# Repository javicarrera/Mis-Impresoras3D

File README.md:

# Mis-Impresoras3D
Recursos para mis impresoras

Para recursos que ocupen mucho hay que proceder de otra forma, a través de la Git Large File Storage. 

1. Instalar https://git-lfs.github.com/
2. Iniciar git lfs 'git lfs install'
   
Hasta aquí se hace para cada cuenta de usuario 
A partir de ahora en cada repositorio hay que seleccionar el tipo de arquivos que quieres que maneje el LFS

'git lfs track "*.psd"'
'git lfs track "*.STEP"'
...
Añadir a git el archivo .gitattributes que ha sido creado automáticamente:
'git add .gitattributes'

Commit & push a Github como siempre...
'''
git add file.psd
git commit -m "Add design file"
git push origin main
'''

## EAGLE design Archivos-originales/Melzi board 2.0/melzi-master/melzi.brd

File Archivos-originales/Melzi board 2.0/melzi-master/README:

Melzi Ardentissimo
Based on Sanguinololu

Schematic and board files.

http://reprap.org/wiki/Melzi

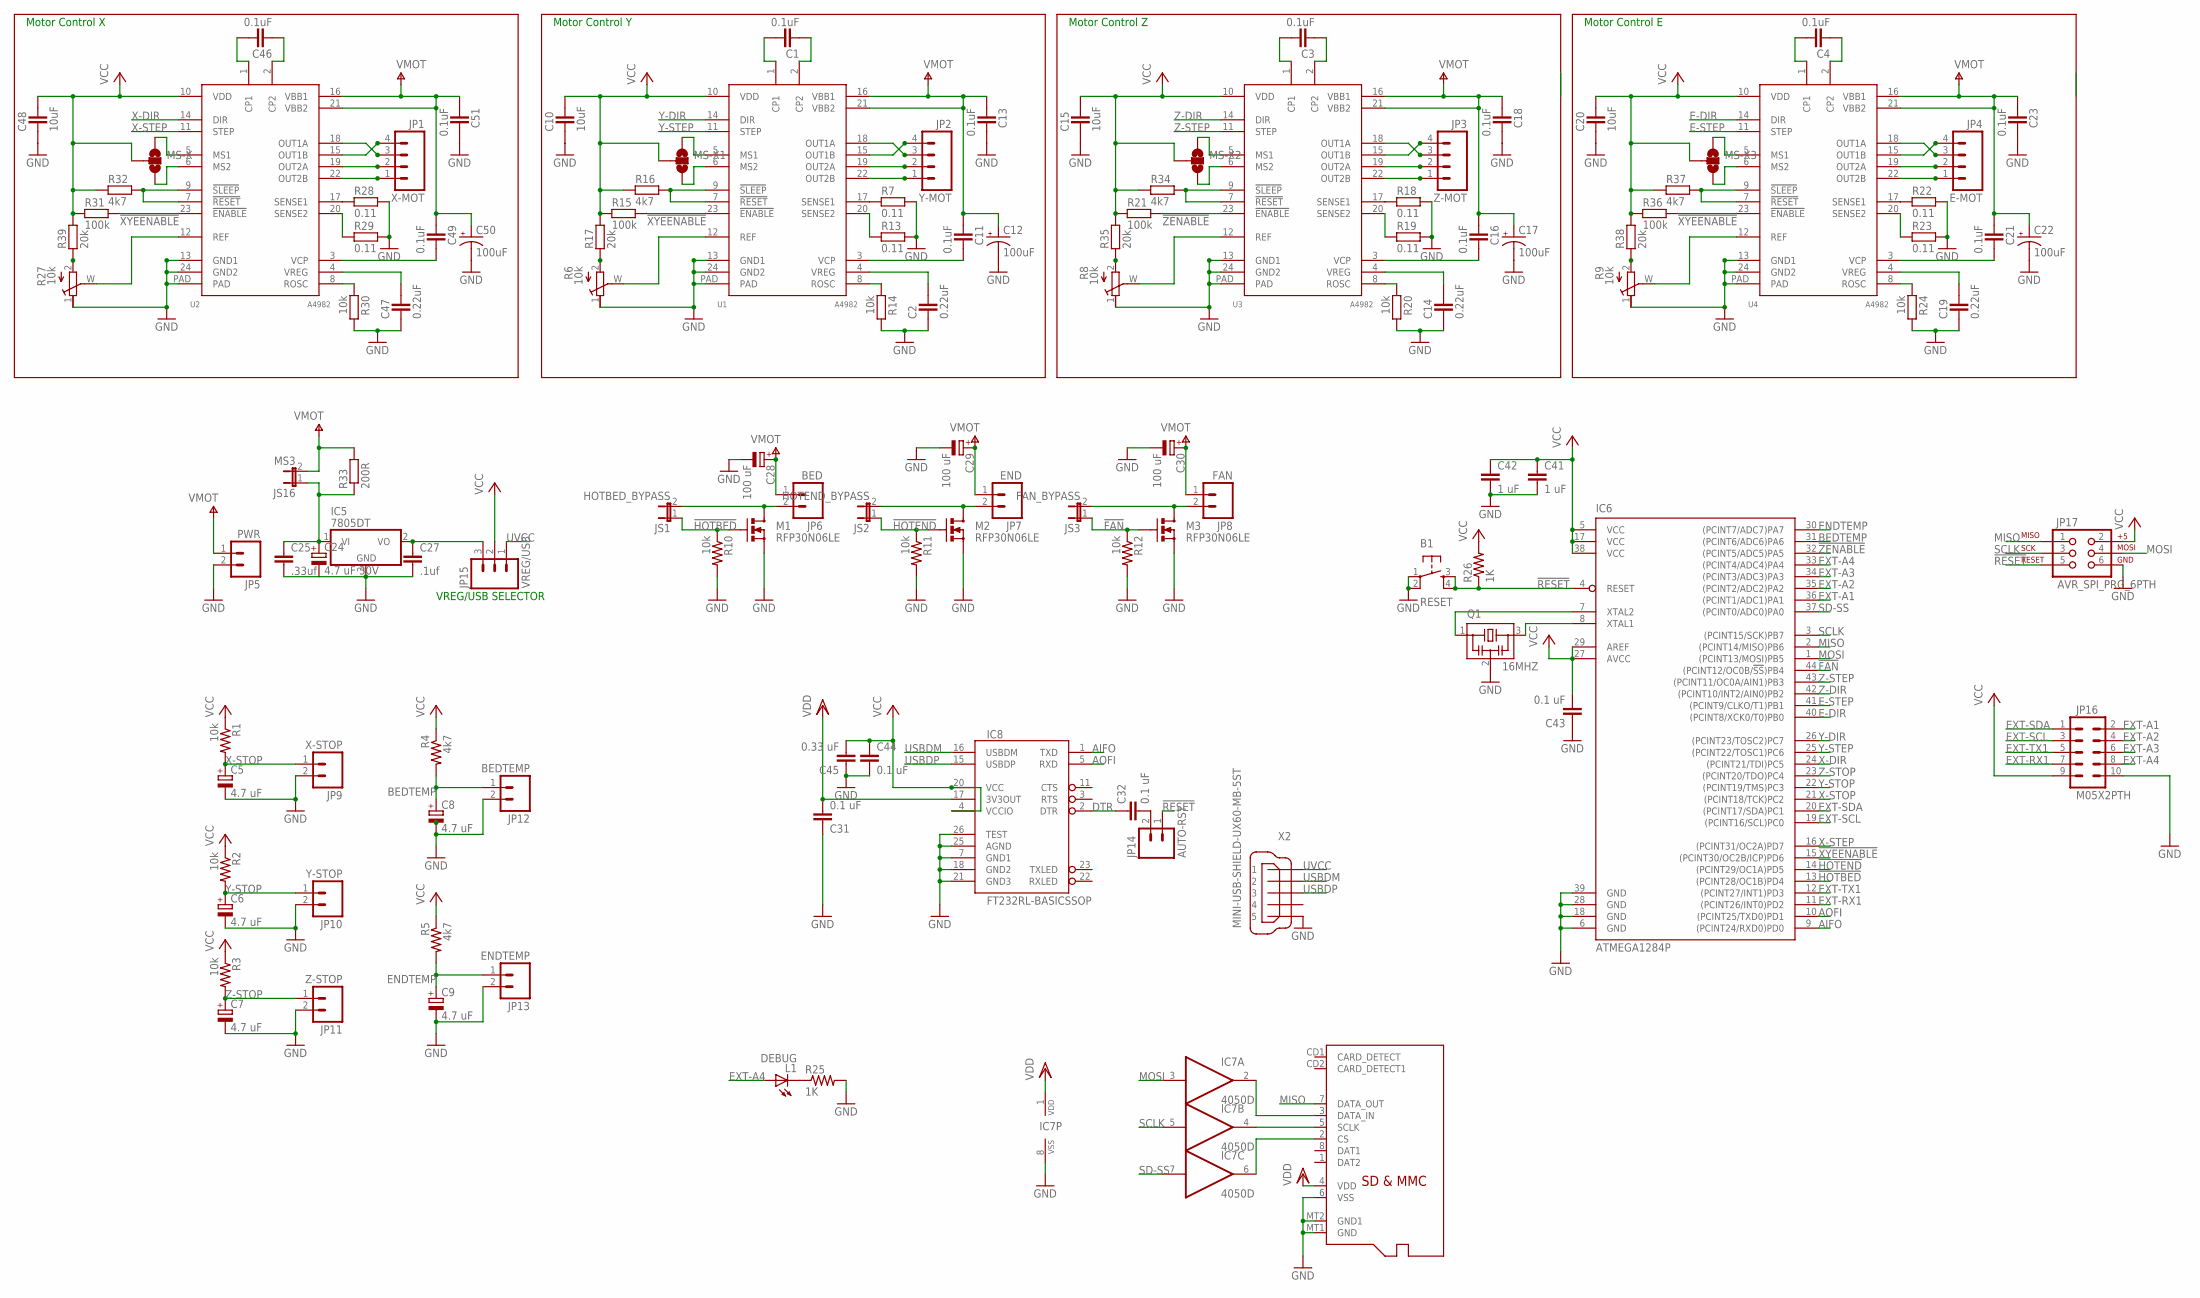
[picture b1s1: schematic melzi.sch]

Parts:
B1: RESET; TACTILE_SWITCH_SMD
C1, C3, C4, C11, C13, C16, C18, C21, C23, C46, C49, C51: 0.1uF; CAPC2012X145AN
C2, C14, C19, C47: 0.22uF; CAPC2012X145AN
C5, C6, C7, C8, C9: 4.7 uF; SMC_C
C10, C15, C20, C48: 10uF; CAPC2012X145AN
C12, C17, C22, C50: 100uF; PANASONIC_D
C24: 4.7 uF 30V; SMC_C
C25: .33uf; 0805
C27: .1uf; 0805
C28, C29, C30: 100 uF; UD-6,3X7,7_NICHICON
C31, C32, C43, C44: 0.1 uF; C1206
C41, C42: 1 uF; C1206
C45: 0.33 uF; C1206
IC5: 7805DT; TO252
IC6: ATMEGA1284P; TQFP44
IC7: 4050D; SO16
IC8: FT232RL-BASICSSOP; SSOP28DB
JP1: X-MOT; SCREWTERMINAL-3.5MM-4
JP2: Y-MOT; SCREWTERMINAL-3.5MM-4
JP3: Z-MOT; SCREWTERMINAL-3.5MM-4
JP4: E-MOT; SCREWTERMINAL-3.5MM-4
JP5: PWR; SCREWTERMINAL-5MM-2
JP6: BED; SCREWTERMINAL-5MM-2
JP7: END; SCREWTERMINAL-5MM-2
JP8: FAN; SCREWTERMINAL-5MM-2
JP9: X-STOP; SCREWTERMINAL-3.5MM-2
JP10: Y-STOP; SCREWTERMINAL-3.5MM-2
JP11: Z-STOP; SCREWTERMINAL-3.5MM-2
JP12: BEDTEMP; SCREWTERMINAL-3.5MM-2
JP13: ENDTEMP; SCREWTERMINAL-3.5MM-2
JP14: AUTO-RST; 1X02
JP15: VREG/USB; 1X03
JP16: M05X2PTH; AVR_ICSP
JP17: AVR_SPI_PRG_6PTH; 2X3
JS1: HOTBED_BYPASS; SJ_2S-NO
JS2: HOTEND_BYPASS; SJ_2S-NO
JS3: FAN_BYPASS; SJ_2S-NO
JS16: MS3; SJ_2S
L1: DEBUG; LED-1206
M1, M2, M3: RFP30N06LE; DPAK
MS-X, MS-X1, MS-X2, MS-X3: SOLDERJUMPER_2WAYCONNECTED; SJ_3_CONNECTED
Q1: 16MHZ; CSTCR6M
R1, R2, R3, R10, R11, R12: 10k; 1206
R4, R5: 4k7; 1206
R6, R8, R9, R27: 10k; RTRIM-ST4ETB
R7, R13, R18, R19, R22, R23, R28, R29: 0.11; RESC2012X70N
R14, R20, R24, R30: 10k; RESC2012X70N
R15, R21, R31, R36: 100k; RESC2012X70N
R16, R32, R34, R37: 4k7; RESC2012X70N
R17, R35, R38, R39: 20k; RESC2012X70N
R25, R26: 1K; 1206
R33: 200R; 0309V
U1, U2, U3, U4: A4982; TSSOP-24
X1: MICROSD
X2: MINI-USB-SHIELD-UX60-MB-5ST; UX60-MB-5ST

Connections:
!FAN: IC6.44 ((PCINT12/OC0B/!SS!)PB4), JS3.1, M3.1 (G), R12.1
!HOTBED: IC6.13 ((PCINT28/OC1B)PD4), JS1.1, M1.1 (G), R10.1
!HOTEND: IC6.14 ((PCINT29/OC1A)PD5), JS2.1, M2.1 (G), R11.1
!RESET: B1.3, B1.4, IC6.4 (RESET), JP14.1, JP17.5, R26.1
!XYEENABLE: IC6.15 ((PCINT30/OC2B/ICP)PD6), R15.2, R31.2, R36.2, U1.23 (!ENABLE), U2.23 (!ENABLE), U4.23 (!ENABLE)
!ZENABLE: IC6.32 ((PCINT5/ADC5)PA5), R21.2, U3.23 (!ENABLE)
AIFO: IC6.9 ((PCINT24/RXD0)PD0), IC8.1 (TXD)
AOFI: IC6.10 ((PCINT25/TXD0)PD1), IC8.5 (RXD)
BEDTEMP: C8.+, IC6.31 ((PCINT6/ADC6)PA6), JP12.1, R4.2
DTR: C32.1, IC8.2 (DTR)
E-DIR: IC6.40 ((PCINT8/XCK0/T0)PB0), U4.14 (DIR)
E-STEP: IC6.41 ((PCINT9/CLKO/T1)PB1), U4.11 (STEP)
ENDTEMP: C9.+, IC6.30 ((PCINT7/ADC7)PA7), JP13.1, R5.2
EXT-A1: IC6.36 ((PCINT1/ADC1)PA1), JP16.2
EXT-A2: IC6.35 ((PCINT2/ADC2)PA2), JP16.4
EXT-A3: IC6.34 ((PCINT3/ADC3)PA3), JP16.6
EXT-A4: IC6.33 ((PCINT4/ADC4)PA4), JP16.8, L1.A
EXT-RX1: IC6.11 ((PCINT26/INT0)PD2), JP16.7
EXT-SCL: IC6.19 ((PCINT16/SCL)PC0), JP16.3
EXT-SDA: IC6.20 ((PCINT17/SDA)PC1), JP16.1
EXT-TX1: IC6.12 ((PCINT27/INT1)PD3), JP16.5
GND: B1.1, B1.2, C2.1, C5.-, C6.-, C7.-, C8.-, C9.-, C10.1, C12.-, C13.2, C14.1, C15.1, C17.-, C18.2, C19.1, C20.1, C22.-, C23.2, C24.-, C25.2, C27.2, C28.-, C29.-, C30.-, C31.1, C41.2, C42.2, C43.1, C44.2, C45.1, C47.1, C48.1, C50.-, C51.2, IC5.3 (GND), IC6.6 (GND), IC6.18 (GND), IC6.28 (GND), IC6.39 (GND), IC7.8 (VSS), IC8.7 (GND1), IC8.18 (GND2), IC8.21 (GND3), IC8.25 (AGND), IC8.26 (TEST), JP5.2, JP9.2, JP10.2, JP11.2, JP12.2, JP13.2, JP16.10, JP17.6, M1.3 (S), M2.3 (S), M3.3 (S), Q1.2, R6.1 (A), R7.2, R8.1 (A), R9.1 (A), R10.2, R11.2, R12.2, R13.2, R14.2, R18.2, R19.2, R20.2, R22.2, R23.2, R24.2, R25.2, R27.1 (A), R28.2, R29.2, R30.2, U1.13 (GND1), U1.24 (GND2), U1.PAD, U2.13 (GND1), U2.24 (GND2), U2.PAD, U3.13 (GND1), U3.24 (GND2), U3.PAD, U4.13 (GND1), U4.24 (GND2), U4.PAD, X1.6 (VSS), X1.MT1 (GND), X1.MT2 (GND1), X2.5
HOTBED-GND: JP6.2, JS1.2, M1.4 (D)
HOTBED-GND1: JP7.2, JS2.2, M2.4 (D)
HOTBED-GND2: JP8.2, JS3.2, M3.4 (D)
MISO: IC6.2 ((PCINT14/MISO)PB6), JP17.1, X1.7 (DATA_OUT)
MOSI: IC6.1 ((PCINT13/MOSI)PB5), IC7.3 (I), JP17.4
unnamed: C46.2, U2.1 (CP1)
unnamed: L1.C, R25.1
unnamed: C1.2, U1.1 (CP1)
unnamed: C46.1, U2.2 (CP2)
unnamed: R28.1, U2.17 (SENSE1)
unnamed: R29.1, U2.20 (SENSE2)
unnamed: R27.W (S), U2.12 (REF)
unnamed: R30.1, U2.8 (ROSC)
unnamed: C47.2, U2.4 (VREG)
unnamed: R32.2, U2.7 (!RESET), U2.9 (!SLEEP)
unnamed: C1.1, U1.2 (CP2)
unnamed: IC7.2 (O), X1.3 (DATA_IN)
unnamed: IC7.4 (O), X1.5 (SCLK)
unnamed: IC7.6 (O), X1.2 (CS)
unnamed: C27.1, IC5.2 (VO), JP15.3
unnamed: R7.1, U1.17 (SENSE1)
unnamed: R13.1, U1.20 (SENSE2)
unnamed: R6.W (S), U1.12 (REF)
unnamed: R14.1, U1.8 (ROSC)
unnamed: C3.2, U3.1 (CP1)
unnamed: C3.1, U3.2 (CP2)
unnamed: R18.1, U3.17 (SENSE1)
unnamed: C49.2, U2.3 (VCP)
unnamed: C4.2, U4.1 (CP1)
unnamed: C32.2, JP14.2
unnamed: C4.1, U4.2 (CP2)
unnamed: IC6.7 (XTAL2), Q1.1
unnamed: IC6.8 (XTAL1), Q1.3
unnamed: MS-X.1, U2.5 (MS1)
unnamed: MS-X.3, U2.6 (MS2)
unnamed: JP1.3, U2.18 (OUT1A)
unnamed: JP1.4, U2.15 (OUT1B)
unnamed: JP1.2, U2.19 (OUT2A)
unnamed: JP1.1, U2.22 (OUT2B)
unnamed: C24.+, C25.1, IC5.1 (VI), JS16.1, R33.1
unnamed: C2.2, U1.4 (VREG)
unnamed: R16.2, U1.7 (!RESET), U1.9 (!SLEEP)
unnamed: C11.2, U1.3 (VCP)
unnamed: MS-X1.1, U1.5 (MS1)
unnamed: MS-X1.3, U1.6 (MS2)
unnamed: JP2.3, U1.18 (OUT1A)
unnamed: JP2.4, U1.15 (OUT1B)
unnamed: JP2.2, U1.19 (OUT2A)
unnamed: JP2.1, U1.22 (OUT2B)
unnamed: R6.2 (E), R17.1
unnamed: R19.1, U3.20 (SENSE2)
unnamed: R8.W (S), U3.12 (REF)
unnamed: R20.1, U3.8 (ROSC)
unnamed: C14.2, U3.4 (VREG)
unnamed: R34.2, U3.7 (!RESET), U3.9 (!SLEEP)
unnamed: C16.2, U3.3 (VCP)
unnamed: MS-X2.1, U3.5 (MS1)
unnamed: MS-X2.3, U3.6 (MS2)
unnamed: JP3.3, U3.18 (OUT1A)
unnamed: JP3.4, U3.15 (OUT1B)
unnamed: JP3.2, U3.19 (OUT2A)
unnamed: JP3.1, U3.22 (OUT2B)
unnamed: R8.2 (E), R35.1
unnamed: R22.1, U4.17 (SENSE1)
unnamed: R23.1, U4.20 (SENSE2)
unnamed: R9.W (S), U4.12 (REF)
unnamed: R24.1, U4.8 (ROSC)
unnamed: C19.2, U4.4 (VREG)
unnamed: R37.2, U4.7 (!RESET), U4.9 (!SLEEP)
unnamed: C21.2, U4.3 (VCP)
unnamed: MS-X3.1, U4.5 (MS1)
unnamed: MS-X3.3, U4.6 (MS2)
unnamed: R27.2 (E), R39.1
unnamed: JP4.3, U4.18 (OUT1A)
unnamed: JP4.4, U4.15 (OUT1B)
unnamed: JP4.2, U4.19 (OUT2A)
unnamed: JP4.1, U4.22 (OUT2B)
unnamed: R9.2 (E), R38.1
SCLK: IC6.3 ((PCINT15/SCK)PB7), IC7.5 (I), JP17.3
SD-SS: IC6.37 ((PCINT0/ADC0)PA0), IC7.7 (I)
USBDM: IC8.16 (USBDM), X2.2
USBDP: IC8.15 (USBDP), X2.3
UVCC: JP15.1, X2.1
VCC: C10.2, C15.2, C20.2, C41.1, C42.1, C43.2, C44.1, C45.2, C48.2, IC6.5 (VCC), IC6.17 (VCC), IC6.27 (AVCC), IC6.29 (AREF), IC6.38 (VCC), IC8.4 (VCCIO), IC8.20 (VCC), JP15.2, JP16.9, JP17.2, MS-X.2, MS-X1.2, MS-X2.2, MS-X3.2, R1.1, R2.1, R3.1, R4.1, R5.1, R15.1, R16.1, R17.2, R21.1, R26.2, R31.1, R32.1, R34.1, R35.2, R36.1, R37.1, R38.2, R39.2, U1.10 (VDD), U2.10 (VDD), U3.10 (VDD), U4.10 (VDD)
VDD: C31.2, IC7.1 (VDD), IC8.17 (3V3OUT), X1.4 (VDD)
VMOT: C11.1, C12.+, C13.1, C16.1, C17.+, C18.1, C21.1, C22.+, C23.1, C28.+, C29.+, C30.+, C49.1, C50.+, C51.1, JP5.1, JP6.1, JP7.1, JP8.1, JS16.2, R33.2, U1.16 (VBB1), U1.21 (VBB2), U2.16 (VBB1), U2.21 (VBB2), U3.16 (VBB1), U3.21 (VBB2), U4.16 (VBB1), U4.21 (VBB2)
X-DIR: IC6.24 ((PCINT21/TDI)PC5), U2.14 (DIR)
X-STEP: IC6.16 ((PCINT31/OC2A)PD7), U2.11 (STEP)
X-STOP: C5.+, IC6.21 ((PCINT18/TCK)PC2), JP9.1, R1.2
Y-DIR: IC6.26 ((PCINT23/TOSC2)PC7), U1.14 (DIR)
Y-STEP: IC6.25 ((PCINT22/TOSC1)PC6), U1.11 (STEP)
Y-STOP: C6.+, IC6.22 ((PCINT19/TMS)PC3), JP10.1, R2.2
Z-DIR: IC6.42 ((PCINT10/INT2/AIN0)PB2), U3.14 (DIR)
Z-STEP: IC6.43 ((PCINT11/OC0A/AIN1)PB3), U3.11 (STEP)
Z-STOP: C7.+, IC6.23 ((PCINT20/TDO)PC4), JP11.1, R3.2

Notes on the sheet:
VREG/USB SELECTOR
Motor Control X
Motor Control Y
Motor Control Z
Motor Control E

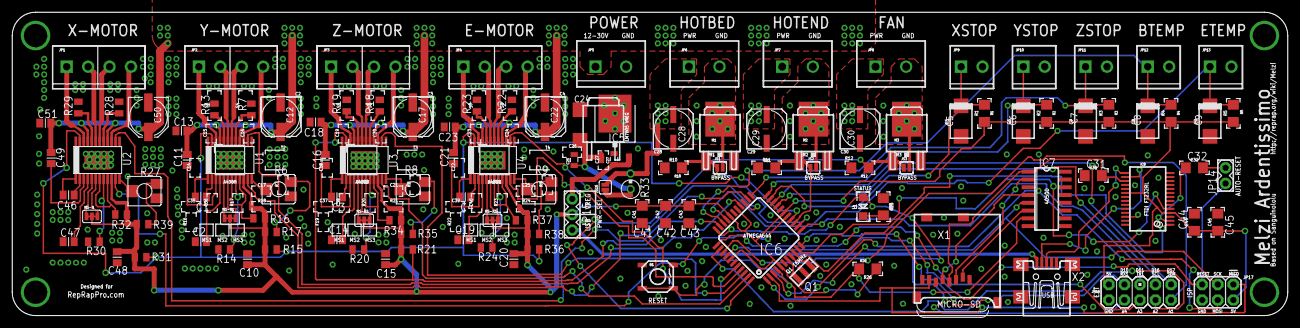
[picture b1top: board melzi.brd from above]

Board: 2 copper layers, 208.3 x 49.5 mm, 122 parts (0 on the bottom side), 117 nets.

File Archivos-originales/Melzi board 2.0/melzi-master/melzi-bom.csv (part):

Partlist

Exported from melzi.sch at 26/07/2012 16:26

EAGLE Version 6.2.0 Copyright (c) 1988-2012 CadSoft

Assembly variant: 

Part     Value                       Device                      Package               Library            Sheet

B1       RESET                       TAC_SWITCHSMD               TACTILE_SWITCH_SMD    SparkFun           1
C1       0.1uF                       CAPACITOR_0805              CAPC2012X145AN        ipc-7351-capacitor 1
C2       0.22uF                      CAPACITOR_0805              CAPC2012X145AN        ipc-7351-capacitor 1
C3       0.1uF                       CAPACITOR_0805              CAPC2012X145AN        ipc-7351-capacitor 1
C4       0.1uF                       CAPACITOR_0805              CAPC2012X145AN        ipc-7351-capacitor 1
C5       4.7 uF                      CPOL-EUSMCC                 SMC_C                 rcl                1
C6       4.7 uF                      CPOL-EUSMCC                 SMC_C                 rcl                1
C7       4.7 uF                      CPOL-EUSMCC                 SMC_C                 rcl                1
C8       4.7 uF                      CPOL-EUSMCC                 SMC_C                 rcl                1
C9       4.7 uF                      CPOL-EUSMCC                 SMC_C                 rcl                1
C10      10uF                        CAPACITOR_0805              CAPC2012X145AN        ipc-7351-capacitor 1
C11      0.1uF                       CAPACITOR_0805              CAPC2012X145AN        ipc-7351-capacitor 1
C12      100uF                       CPOL-USD                    PANASONIC_D           rcl                1
C13      0.1uF                       CAPACITOR_0805              CAPC2012X145AN        ipc-7351-capacitor 1
C14      0.22uF                      CAPACITOR_0805              CAPC2012X145AN        ipc-7351-capacitor 1
C15      10uF                        CAPACITOR_0805              CAPC2012X145AN        ipc-7351-capacitor 1
C16      0.1uF                       CAPACITOR_0805              CAPC2012X145AN        ipc-7351-capacitor 1
C17      100uF                       CPOL-USD                    PANASONIC_D           rcl                1
C18      0.1uF                       CAPACITOR_0805              CAPC2012X145AN        ipc-7351-capacitor 1
C19      0.22uF                      CAPACITOR_0805              CAPC2012X145AN        ipc-7351-capacitor 1
C20      10uF                        CAPACITOR_0805              CAPC2012X145AN        ipc-7351-capacitor 1
C21      0.1uF                       CAPACITOR_0805              CAPC2012X145AN        ipc-7351-capacitor 1
C22      100uF                       CPOL-USD                    PANASONIC_D           rcl                1
C23      0.1uF                       CAPACITOR_0805              CAPC2012X145AN        ipc-7351-capacitor 1
C24      4.7 uF 30V                  CPOL-EUSMCC                 SMC_C                 rcl                1
C25      .33uf                       CAP0805                     0805                  SparkFun           1
C27      .1uf                        CAP0805                     0805                  SparkFun           1
C28      100 uF                      CPOL-EUUD-6,3X7,7           UD-6,3X7,7_NICHICON   rcl                1
C29      100 uF                      CPOL-EUUD-6,3X7,7           UD-6,3X7,7_NICHICON   rcl                1
C30      100 uF                      CPOL-EUUD-6,3X7,7           UD-6,3X7,7_NICHICON   rcl                1
C31      0.1 uF                      C-EUC1206                   C1206                 rcl                1
C32      0.1 uF                      C-EUC1206                   C1206                 rcl                1
C41      1 uF                        C-EUC1206                   C1206                 rcl                1
C42      1 uF                        C-EUC1206                   C1206                 rcl                1
C43      0.1 uF                      C-EUC1206                   C1206                 rcl                1
C44      0.1 uF                      C-EUC1206                   C1206                 rcl                1
C45      0.33 uF                     C-EUC1206                   C1206                 rcl                1
C46      0.1uF                       CAPACITOR_0805              CAPC2012X145AN        ipc-7351-capacitor 1
C47      0.22uF                      CAPACITOR_0805              CAPC2012X145AN        ipc-7351-capacitor 1
C48      10uF                        CAPACITOR_0805              CAPC2012X145AN        ipc-7351-capacitor 1
C49      0.1uF                       CAPACITOR_0805              CAPC2012X145AN        ipc-7351-capacitor 1
C50      100uF                       CPOL-USD                    PANASONIC_D           rcl                1
C51      0.1uF                       CAPACITOR_0805              CAPC2012X145AN        ipc-7351-capacitor 1
IC5      7805DT                      7805DT                      TO252                 linear             1
IC6      ATMEGA1284P                 ATMEGA644A                  TQFP44                atmel              1
IC7      4050D                       4050D                       SO16                  40xx               1
IC8      FT232RL-BASICSSOP           FT232RL-BASICSSOP           SSOP28DB              SparkFun           1
JP1      X-MOT                       M04SCREW                    SCREWTERMINAL-3.5MM-4 SparkFun           1
JP2      Y-MOT                       M04SCREW                    SCREWTERMINAL-3.5MM-4 SparkFun           1
JP3      Z-MOT                       M04SCREW                    SCREWTERMINAL-3.5MM-4 SparkFun           1
JP4      E-MOT                       M04SCREW                    SCREWTERMINAL-3.5MM-4 SparkFun           1
JP5      PWR                         M025MM                      SCREWTERMINAL-5MM-2   SparkFun           1
JP6      BED                         M025MM                      SCREWTERMINAL-5MM-2   SparkFun           1
JP7      END                         M025MM                      SCREWTERMINAL-5MM-2   SparkFun           1
JP8      FAN                         M025MM                      SCREWTERMINAL-5MM-2   SparkFun           1
JP9      X-STOP                      M023.5MM                    SCREWTERMINAL-3.5MM-2 SparkFun           1
JP10     Y-STOP                      M023.5MM                    SCREWTERMINAL-3.5MM-2 SparkFun           1
JP11     Z-STOP                      M023.5MM                    SCREWTERMINAL-3.5MM-2 SparkFun           1
JP12     BEDTEMP                     M023.5MM                    SCREWTERMINAL-3.5MM-2 SparkFun           1
JP13     ENDTEMP                     M023.5MM                    SCREWTERMINAL-3.5MM-2 SparkFun           1
JP14     AUTO-RST                    M02PTH                      1X02                  SparkFun           1
JP15     VREG/USB                    M03PTH                      1X03                  SparkFun           1
JP16     M05X2PTH                    M05X2PTH                    AVR_ICSP              SparkFun           1
JP17     AVR_SPI_PRG_6PTH            AVR_SPI_PRG_6PTH            2X3                   SparkFun           1
JS1      HOTBED_BYPASS               JUMPER-2SMD-NO              SJ_2S-NO              SparkFun           1
JS2      HOTEND_BYPASS               JUMPER-2SMD-NO              SJ_2S-NO              SparkFun           1
JS3      FAN_BYPASS                  JUMPER-2SMD-NO              SJ_2S-NO              SparkFun           1
JS16     MS3                         JUMPER-2SMD-NC              SJ_2S                 SparkFun           1
L1       DEBUG                       LED1206                     LED-1206              SparkFun           1
M1       RFP30N06LE                  MOSFET-NCHANNELFDD8580      DPAK                  SparkFun           1
M2       RFP30N06LE                  MOSFET-NCHANNELFDD8580      DPAK                  SparkFun           1
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
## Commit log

2021-08-16 Estructura del master
2021-08-16 Tronxy-archivos originales
2021-08-16 videos añadidos
2021-08-16 Delta archivos originales
2021-08-16 Añadidos archivos originales
2021-08-16 Archivos originales
2021-08-16 Perfiles de CURA
2021-08-20 Create Calibracion-Cartesiana

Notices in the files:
Archivos-originales/Melzi board 2.0/melzi-master/melzi.brd:
reprappro.com RepRap Melzi V2.0  Licence: GPL Design: Joe Mosfet & Adrian
